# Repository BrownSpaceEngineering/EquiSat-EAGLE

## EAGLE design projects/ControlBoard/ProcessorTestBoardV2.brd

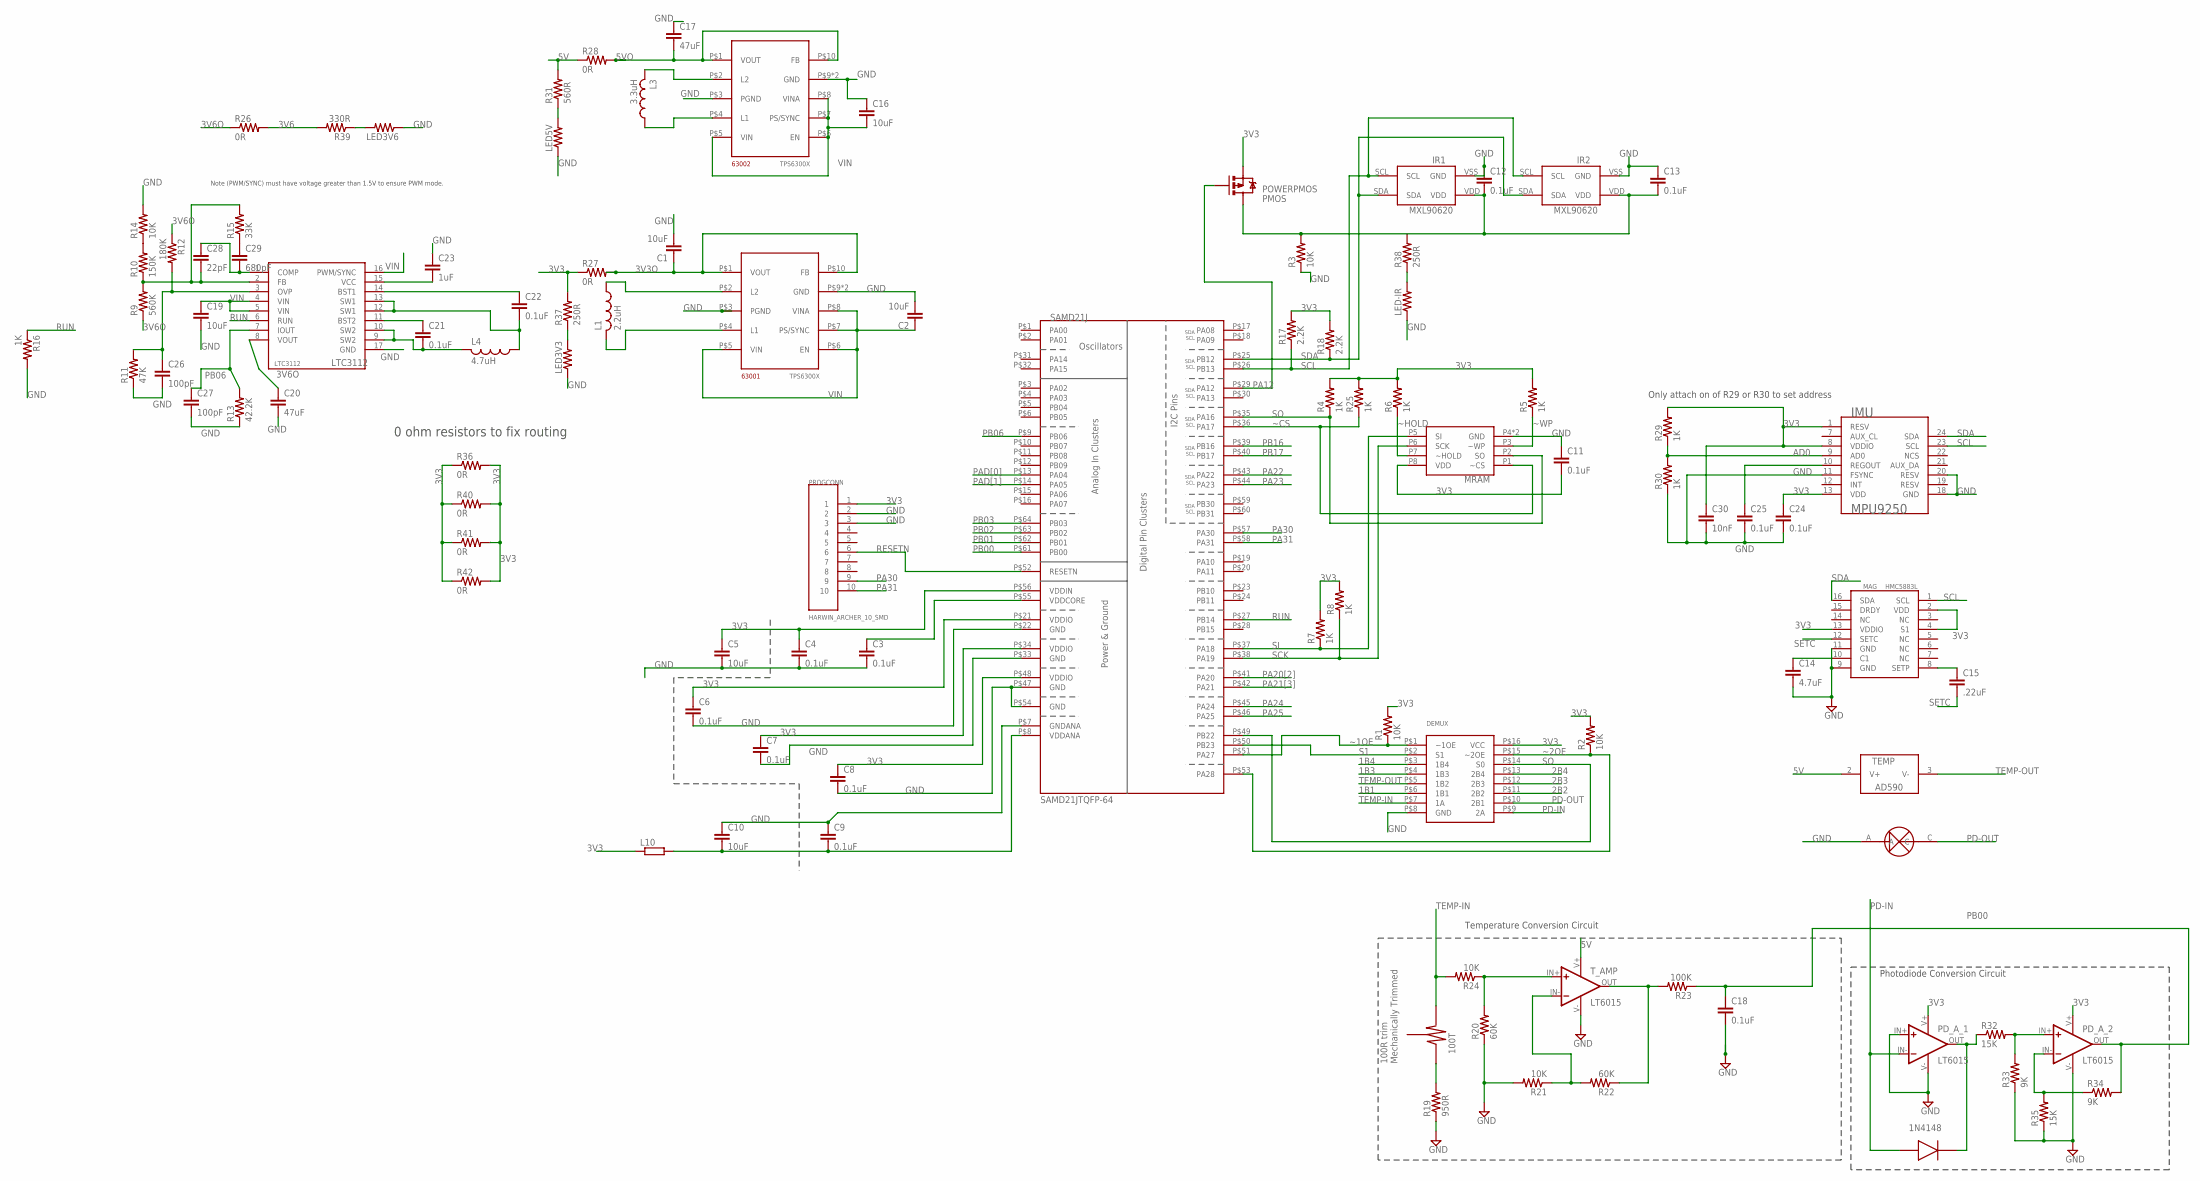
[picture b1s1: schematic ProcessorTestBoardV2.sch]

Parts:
1N4148: 1N4148WS; SOD-323F
100T: TRIMPOT-TC33; TC33X-2
63001, 63002: TPS6300X; QFN10_POWERPAD
C1, C2, C5, C10: 10uF; 0805
C3, C4, C6, C7, C8, C9, C11, C12, C13, C18, C24, C25: 0.1uF; 0805
C14: 4.7uF; 0805; MPN 08056D475KAT2A
C15: .22uF; 0805; MPN 08053C224KAT2A
C16: 10uF; 0603-CAP; MPN C1608X5R1A225K080AC
C17: 47uF; 0603-CAP; MPN EMK107B7474KA-T
C19: 10uF; 0603-CAP
C20: 47uF; 0805; MPN EMK107B7474KA-T
C21, C22: 0.1uF; 0603-CAP; MPN 0603YC104JAT2A
C23: 1uF; 0603-CAP
C26, C27: 100pF; 0805; MPN 08051A101J4T4A
C28: 22pF; 0805; MPN 08051A220JAT2A
C29: 680pF; 0805; MPN 08055C681KAT2A
C30: 10nF; 0805
DEMUX: SN74CBTLV3253; SOIC16R
IMU: MPU9250; QFN-24-3X3
IR1, IR2: MXL90620
L1: 2.2uH; L3225M
L3: 3.3uH; L3225M; MPN JMK212BJ335KG-T
L4: 4.7uH; L3225M
L10: R-EU_R0805; R0805
LED3V3, LED3V6, LED5V: RESISTOR; 0805
LED-IR: RESISTOR; 0805
LTC3112: LTC3112; DHD16; MPN LTC3112EFE#PBF
MAG: HMC5883L; MPN HMC5883L-TR
MRAM: MR25H10CDC; 8PXMO-229
PD: PHOTODETECTOR; PHOTODECTORDEVICE2
PD_A_1, PD_A_2: LT6015; SOT23-5
PMOS: POWERPMOS; SO08
PROGCONN: HARWIN_ARCHER_10_SMD
R1, R2, R3, R14, R21, R24: 10K; 0805
R4, R5, R6, R7, R8, R16, R25, R29, R30: 1K; 0805
R9: 560K; 0805; MPN MC01W08051560K
R10: 150K; 0805
R11: 47K; 0805
R12: 180K; 0805; MPN ERJ-6GEYJ184V
R13: 42.2K; 0805
R15: 33K; 0805
R17, R18: 2.2K; 0805; MPN SR1-0805-222
R19: 950R; 0805
R20, R22: 60K; 0805
R23: 100K; 0805
R26, R27, R28, R36, R40, R41, R42: 0R; 0805
R31: 560R; 0805
R32, R35: 15K; 0805
R33, R34: 9K; 0805
R37, R38: 250R; 0805
R39: 330R; 0805
SAMD21J: SAMD21JTQFP-64; TQFP-64
TEMP: AD590; 8SOIC
T_AMP: LT6015; SOT23-5

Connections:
1B1: DEMUX.P$6 (1B1)
1B3: DEMUX.P$4 (1B3)
1B4: DEMUX.P$3 (1B4)
2B2: DEMUX.P$11 (2B2)
2B3: DEMUX.P$12 (2B3)
2B4: DEMUX.P$13 (2B4)
3V3: C4.1, C5.1, C6.1, C7.1, C8.1, C11.2, C24.1, C30.1, DEMUX.P$16 (VCC), IMU.1 (RESV), IMU.8 (VDDIO), IMU.13 (VDD), L10.1, MAG.2 (VDD), MAG.4 (S1), MAG.13 (VDDIO), MRAM.P8 (VDD), PD_A_1.V+, PD_A_2.V+, PMOS.1 (S), PMOS.2 (S), PMOS.3 (S), PROGCONN.1, R1.2, R2.2, R4.2, R5.2, R6.2, R7.2, R8.2, R17.2, R18.2, R25.2, R27.1, R29.2, R36.1, R36.2, R37.2, R40.1, R40.2, R41.1, R41.2, R42.1, R42.2, SAMD21J.P$21 (VDDIO), SAMD21J.P$34 (VDDIO), SAMD21J.P$48 (VDDIO), SAMD21J.P$56 (VDDIN)
3V3O: 63001.P$1 (VOUT), 63001.P$10 (FB), C1.1, R27.2
3V6: R26.2, R39.2
3V6O: C20.1, LTC3112.8 (VOUT), R9.1, R12.1, R26.1
5V: R28.1, R31.2, TEMP.2 (V+), T_AMP.V+
5VO: 63002.P$1 (VOUT), 63002.P$10 (FB), C17.2, R28.2
AD0: IMU.9 (AD0), R29.1, R30.2
GND: 63001.P$3 (PGND), 63001.P$9 (GND), 63001.PAD (GND), 63002.P$3 (PGND), 63002.P$9 (GND), 63002.PAD (GND), C1.2, C2.2, C3.2, C4.2, C5.2, C6.2, C7.2, C8.2, C9.1, C10.1, C11.1, C12.1, C13.1, C14.2, C16.1, C17.1, C18.2, C19.2, C20.2, C23.1, C24.2, C25.2, C26.2, C27.2, C30.2, DEMUX.P$8 (GND), IMU.11 (FSYNC), IMU.18 (GND), IMU.20 (RESV), IR1.VSS (GND), IR2.VSS (GND), LED3V3.1, LED3V6.1, LED5V.1, LED-IR.1, LTC3112.17 (GND), MAG.9 (GND), MAG.11 (GND), MRAM.P4 (GND), MRAM.P9 (GND), PD.A, PD_A_1.IN+, PD_A_1.V-, PD_A_2.V-, PROGCONN.2, PROGCONN.3, R3.1, R11.1, R13.1, R14.2, R16.2, R19.1, R20.1, R21.2, R30.1, R33.1, R35.1, SAMD21J.P$7 (GNDANA), SAMD21J.P$22 (GND), SAMD21J.P$33 (GND), SAMD21J.P$47 (GND), SAMD21J.P$54 (GND), T_AMP.V-
unnamed: C12.2, C13.2, IR1.VDD, IR2.VDD, PMOS.5 (D), PMOS.6 (D), PMOS.7 (D), PMOS.8 (D), R3.2
unnamed: 63001.P$4 (L1), L1.2
unnamed: 63001.P$2 (L2), L1.1
unnamed: C21.1, LTC3112.11 (BST2)
unnamed: C22.1, LTC3112.14 (BST1)
unnamed: C23.2, LTC3112.15 (VCC)
unnamed: C14.1, MAG.10 (C1)
unnamed: C3.1, SAMD21J.P$55 (VDDCORE)
unnamed: R20.2, R24.1, T_AMP.IN+
unnamed: R22.1, R23.2, T_AMP.OUT
unnamed: R21.1, R22.2, T_AMP.IN-
unnamed: 1N4148.CATHODE, PD_A_1.OUT, R32.1
unnamed: 100T.P$1 (1), R19.2
unnamed: C25.1, IMU.10 (REGOUT)
unnamed: PD_A_2.IN+, R32.2, R33.2
unnamed: LED-IR.2, R38.1
unnamed: C9.2, C10.2, L10.2, SAMD21J.P$8 (VDDANA)
unnamed: PD_A_2.IN-, R34.1, R35.2
unnamed: LED3V6.2, R39.1
unnamed: LED5V.2, R31.1
unnamed: LED3V3.2, R37.1
unnamed: C15.1, MAG.8 (SETP)
unnamed: C22.2, L4.1, LTC3112.12 (SW1), LTC3112.13 (SW1)
unnamed: 63002.P$2 (L2), L3.2
unnamed: 63002.P$4 (L1), L3.1
unnamed: C21.2, L4.2, LTC3112.9 (SW2), LTC3112.10 (SW2)
unnamed: C28.2, LTC3112.2 (FB), R9.2, R10.1, R15.2
unnamed: C26.1, LTC3112.3 (OVP), R11.2, R12.2
unnamed: C29.1, R15.1
unnamed: C28.1, C29.2, LTC3112.1 (COMP)
unnamed: R10.2, R14.1
PA12: PMOS.4 (G), SAMD21J.P$29 (PA12)
PA20[2]: SAMD21J.P$41 (PA20)
PA21[3]: SAMD21J.P$42 (PA21)
PA22: SAMD21J.P$43 (PA22)
PA23: SAMD21J.P$44 (PA23)
PA24: SAMD21J.P$45 (PA24)
PA25: SAMD21J.P$46 (PA25)
PA30: PROGCONN.9, SAMD21J.P$57 (PA30)
PA31: PROGCONN.10, SAMD21J.P$58 (PA31)
PAD[0]: SAMD21J.P$13 (PA04)
PAD[1]: SAMD21J.P$14 (PA05)
PB00: C18.1, PD_A_2.OUT, R23.1, R34.2, SAMD21J.P$61 (PB00)
PB01: SAMD21J.P$62 (PB01)
PB02: SAMD21J.P$63 (PB02)
PB03: SAMD21J.P$64 (PB03)
PB06: C27.1, LTC3112.7 (IOUT), R13.2, SAMD21J.P$9 (PB06)
PB16: SAMD21J.P$39 (PB16)
PB17: SAMD21J.P$40 (PB17)
PD-IN: 1N4148.ANODE, DEMUX.P$9 (2A), PD_A_1.IN-
PD-OUT: DEMUX.P$10 (2B1), PD.C
RESETN: PROGCONN.6, SAMD21J.P$52 (RESETN)
RUN: LTC3112.6 (RUN), R16.1, SAMD21J.P$27 (PB14)
S1: DEMUX.P$2 (S1), SAMD21J.P$50 (PB23)
SCK: MRAM.P6 (SCK), R8.1, SAMD21J.P$38 (PA19)
SCL: IMU.23 (SCL), IR1.SCL, IR2.SCL, MAG.1 (SCL), R17.1, SAMD21J.P$26 (PB13)
SDA: IMU.24 (SDA), IR1.SDA, IR2.SDA, MAG.16 (SDA), R18.1, SAMD21J.P$25 (PB12)
SETC: C15.2, MAG.12 (SETC)
SI: MRAM.P5 (SI), R7.1, SAMD21J.P$37 (PA18)
SO: DEMUX.P$14 (S0), MRAM.P2 (SO), R4.1, SAMD21J.P$35 (PA16), SAMD21J.P$49 (PB22)
TEMP-IN: 100T.P$3 (3), DEMUX.P$7 (1A), R24.2
TEMP-OUT: DEMUX.P$5 (1B2), TEMP.3 (V-)
VIN: 63001.P$5 (VIN), 63001.P$6 (EN), 63001.P$7 (PS/SYNC), 63001.P$8 (VINA), 63002.P$5 (VIN), 63002.P$6 (EN), 63002.P$7 (PS/SYNC), 63002.P$8 (VINA), C2.1, C16.2, C19.1, LTC3112.4 (VIN), LTC3112.5 (VIN), LTC3112.16 (PWM/SYNC)
~1OE: DEMUX.P$1 (~1OE), R1.1, SAMD21J.P$51 (PA27)
~2OE: DEMUX.P$15 (~2OE), R2.1, SAMD21J.P$53 (PA28)
~CS: MRAM.P1 (~CS), R25.1, SAMD21J.P$36 (PA17)
~HOLD: MRAM.P7 (~HOLD), R6.1
~WP: MRAM.P3 (~WP), R5.1

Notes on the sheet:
Note (PWM/SYNC) must have voltage greater than 1.5V to ensure PWM mode.
Temperature Conversion Circuit
100R trim Mechanically Trimmed
Photodiode Conversion Circuit
Only attach on of R29 or R30 to set address
0 ohm resistors to fix routing

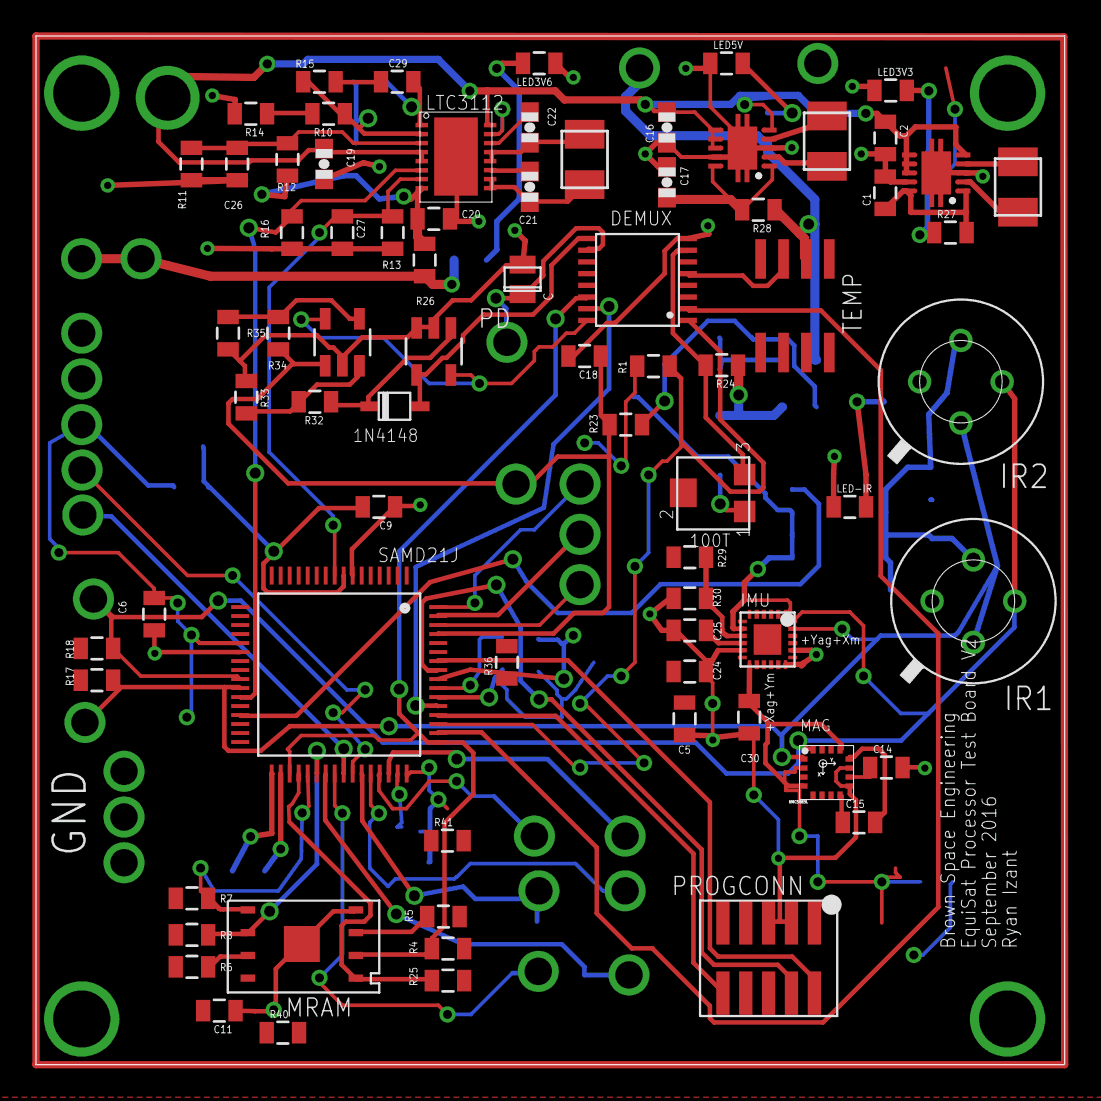
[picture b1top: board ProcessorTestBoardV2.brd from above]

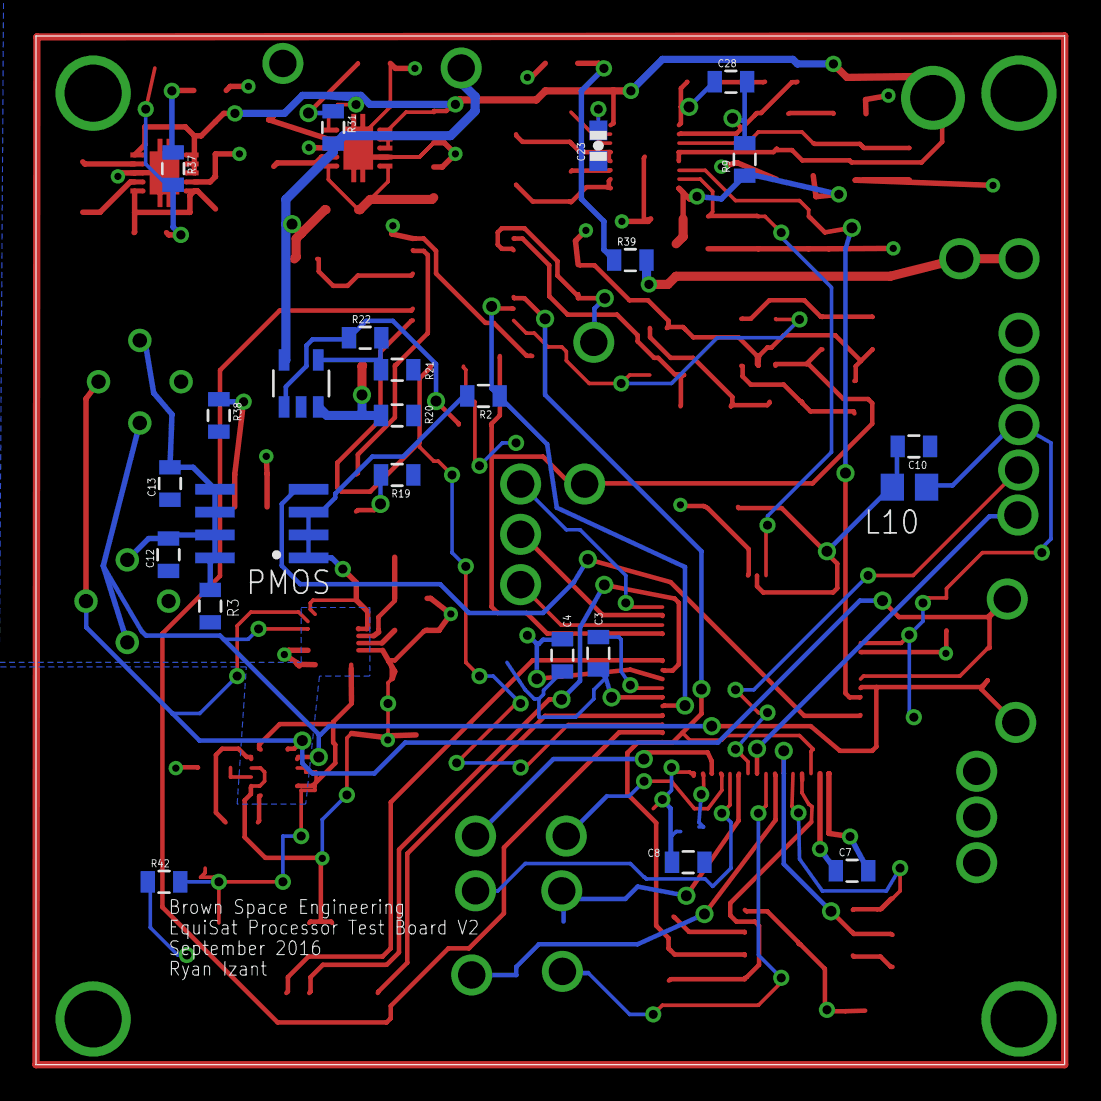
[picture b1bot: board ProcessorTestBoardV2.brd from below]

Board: 2 copper layers, 57.1 x 57.1 mm, 99 parts (24 on the bottom side), 63 nets.

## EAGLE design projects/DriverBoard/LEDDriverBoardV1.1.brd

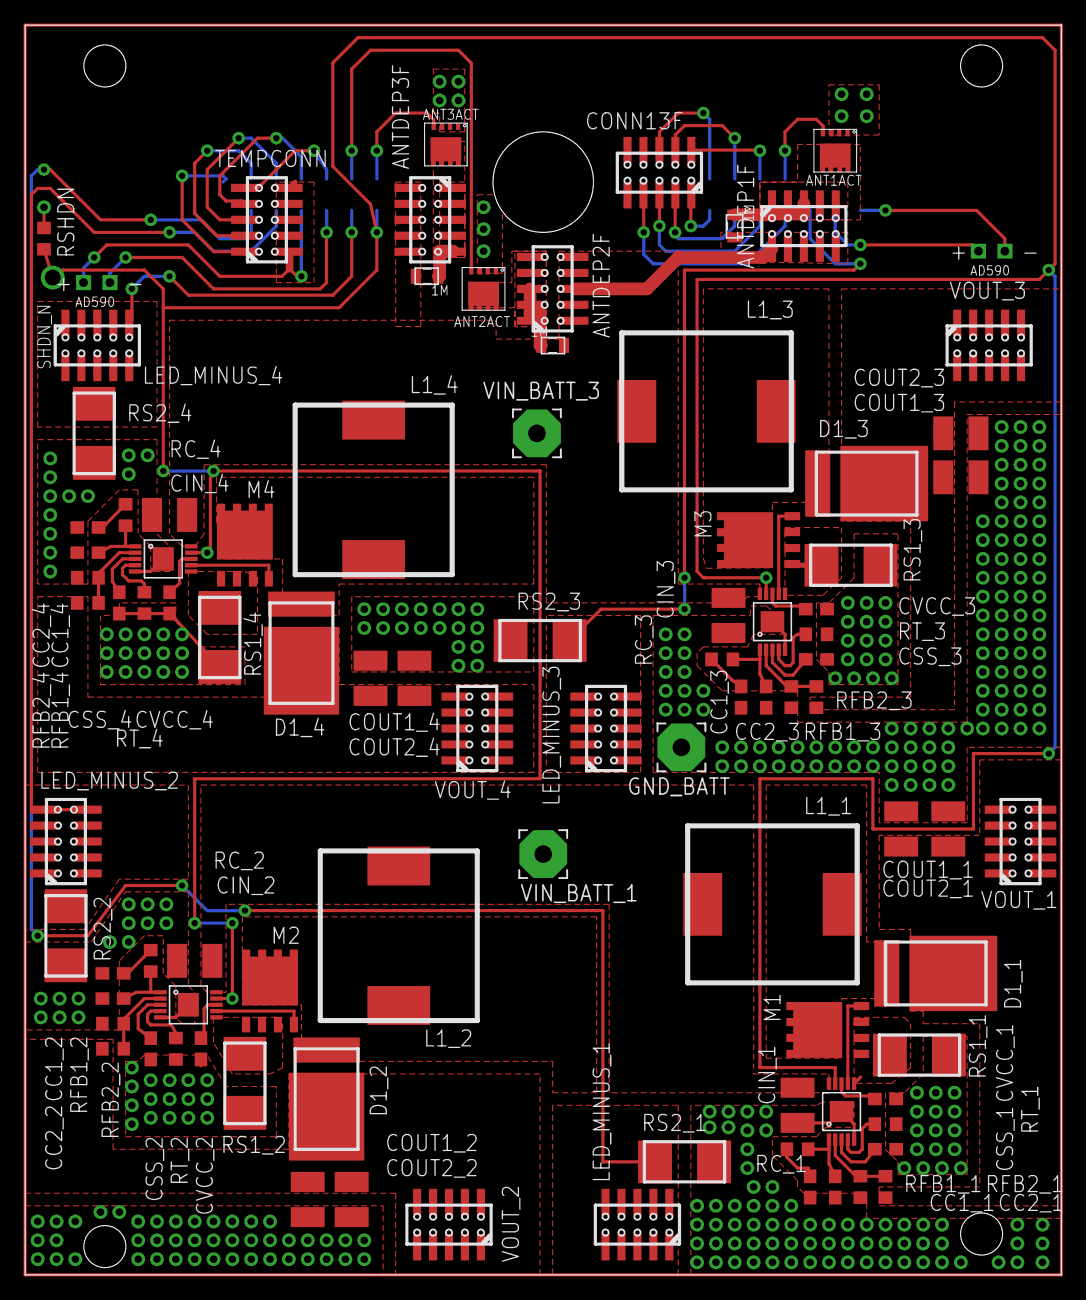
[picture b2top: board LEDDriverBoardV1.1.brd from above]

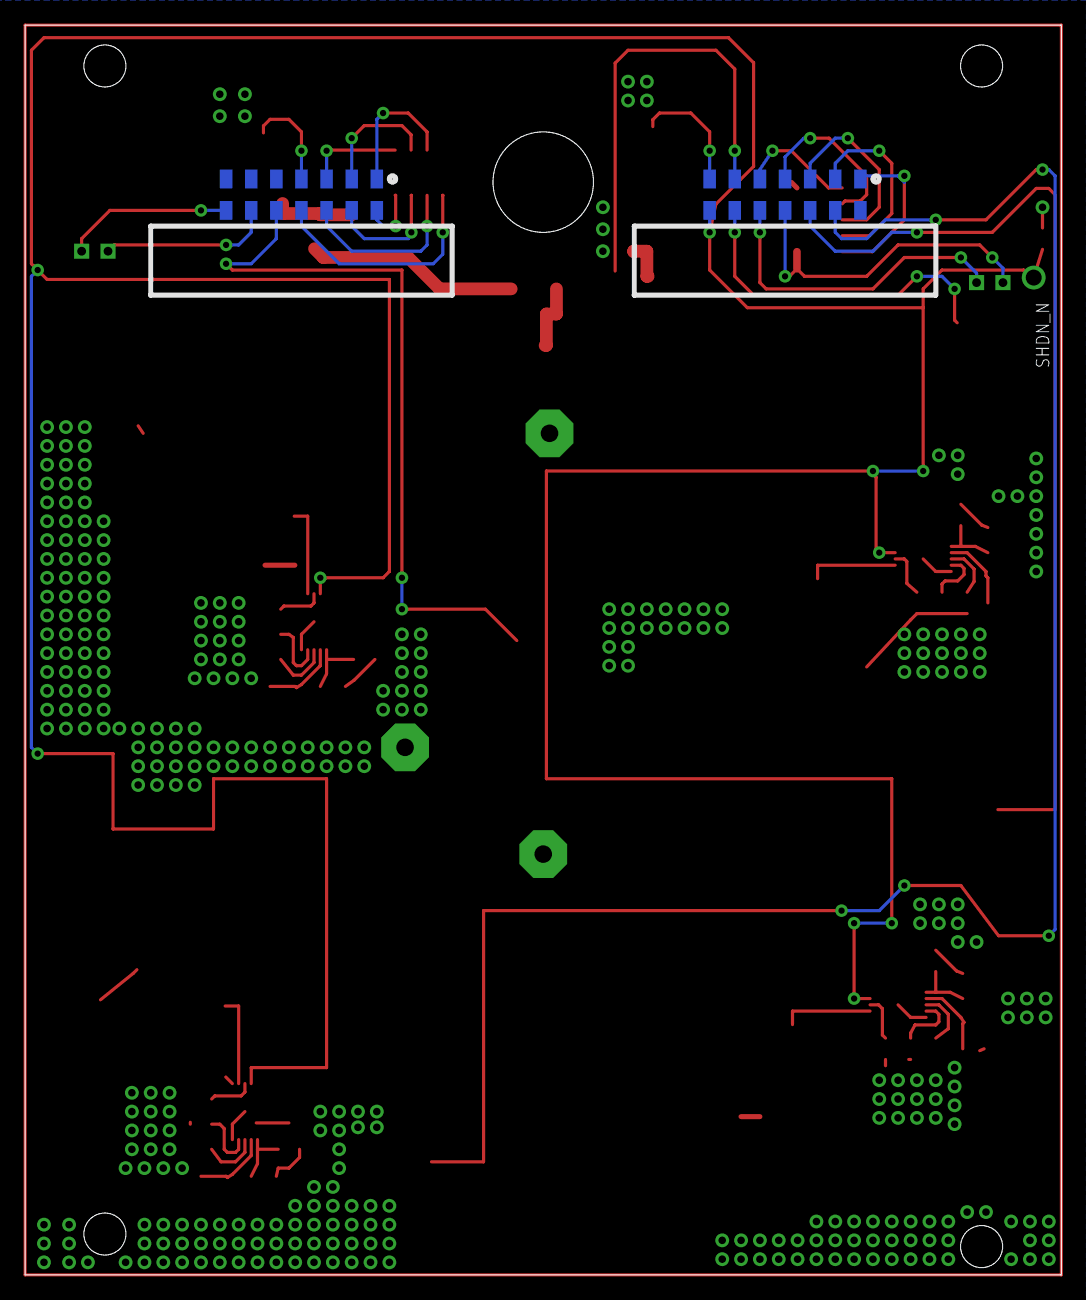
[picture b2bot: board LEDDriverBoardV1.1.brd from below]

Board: 2 copper layers, 82.5 x 99.5 mm, 95 parts (2 on the bottom side), 70 nets.

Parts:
ANT1ACT, ANT2ACT, ANT3ACT: AON7292; DFN3.3X3.3
ANTDEP1F, ANTDEP2F, ANTDEP3F: 10PINFEMALE
CC1_1, CC1_2, CC1_3, CC1_4: 22n; C0603
CC2_1, CC2_2, CC2_3, CC2_4: 100p; C0603
CIN_1, CIN_2, CIN_3, CIN_4: 10u; C1210
CONN13F: 10PINFEMALE
COUT1_1, COUT1_2, COUT1_3, COUT1_4, COUT2_1, COUT2_2, COUT2_3, COUT2_4: 10u; C1210
CSS_1, CSS_2, CSS_3, CSS_4: 0.1u; C0603
CVCC_1, CVCC_2, CVCC_3, CVCC_4: 4.7u; C0603
D1_1, D1_2, D1_3, D1_4: SMC(Z5-T)
DRIVE3TEMP, DRIVE4TEMP: AD590-TH; AD590TH
DRIVECONN1, DRIVECONN2: HARWIN_14_HORIZONTAL_SMD; 14PINMALE_SMD
GND_BATT: 3,81/1,4
L1_1, L1_2, L1_3, L1_4: 1.5u; SRP1245A
LED_MINUS_1, LED_MINUS_2, LED_MINUS_3, LED_MINUS_4: 10PINFEMALE
M1, M2, M3, M4: POWERFLAT
R1, R2, R3: 1M; 0805
RC_1, RC_2, RC_4: 10k; R0603
RC_3: 10K; R0603
RFB1_1, RFB1_2, RFB1_3, RFB1_4: 1k; R0603
RFB2_1, RFB2_2, RFB2_3, RFB2_4: 22.125k; R0603
RS1_1, RS1_2, RS1_3, RS1_4, RS2_1, RS2_2, RS2_3, RS2_4: 3m; ERJMS4S
RSHDN: 1k; R0603
RT_1, RT_2, RT_3, RT_4: 24.3k; R0603
TEMPCONN: 10PINFEMALE
U1, U2, U3, U4: MSOP10
VIN_BATT_1, VIN_BATT_3: 3,81/1,4
VOUT_1, VOUT_2, VOUT_3, VOUT_4: 10PINFEMALE

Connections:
5V_1: DRIVE4TEMP.P$1, DRIVECONN1.11, TEMPCONN.6, TEMPCONN.7, TEMPCONN.8, TEMPCONN.9, TEMPCONN.10
5V_2: DRIVE3TEMP.P$1, DRIVECONN2.9
FBX_1: RFB1_1.2, RFB2_1.1, U1.P$2
FBX_2: RFB1_2.2, RFB2_2.1, U2.P$2
FBX_3: RFB1_3.2, RFB2_3.1, U3.P$2
FBX_4: RFB1_4.2, RFB2_4.1, U4.P$2
FET_SENSE_1: M1.S1, M1.S2, M1.S3, RS1_1.A, U1.P$6
FET_SENSE_2: M2.S1, M2.S2, M2.S3, RS1_2.A, U2.P$6
FET_SENSE_3: M3.S1, M3.S2, M3.S3, RS1_3.A, U3.P$6
FET_SENSE_4: M4.S1, M4.S2, M4.S3, RS1_4.A, U4.P$6
GATE_1: M1.G, U1.P$7
GATE_2: M2.G, U2.P$7
GATE_3: M3.G, U3.P$7
GATE_4: M4.G, U4.P$7
GND: ANT1ACT.S1, ANT1ACT.S2, ANT1ACT.S3, ANT2ACT.S1, ANT2ACT.S2, ANT2ACT.S3, ANT3ACT.S1, ANT3ACT.S2, ANT3ACT.S3, CC1_1.2, CC1_2.2, CC1_3.2, CC1_4.2, CC2_1.2, CC2_2.2, CC2_3.2, CC2_4.2, CIN_1.2, CIN_2.2, CIN_3.2, CIN_4.2, COUT1_1.2, COUT1_2.2, COUT1_3.2, COUT1_4.2, COUT2_1.2, COUT2_2.2, COUT2_3.2, COUT2_4.2, CSS_1.2, CSS_2.2, CSS_3.2, CSS_4.2, CVCC_1.2, CVCC_2.2, CVCC_3.2, CVCC_4.2, DRIVECONN1.14, GND_BATT.1, RFB1_1.1, RFB1_2.1, RFB1_3.1, RFB1_4.1, RS1_1.B, RS1_2.B, RS1_3.B, RS1_4.B, RS2_1.B, RS2_2.B, RS2_3.B, RS2_4.B, RSHDN.1, RT_1.1, RT_2.1, RT_3.1, RT_4.1, U1.P$5, U1.P$11, U2.P$5, U2.P$11, U3.P$5, U3.P$11, U4.P$5, U4.P$11
G_ANT1: ANT1ACT.G, DRIVECONN2.4
G_ANT2: ANT2ACT.G, DRIVECONN1.6
G_ANT3: ANT3ACT.G, DRIVECONN1.7
INTVCC_1: CVCC_1.1, U1.P$8
INTVCC_2: CVCC_2.1, U2.P$8
INTVCC_3: CVCC_3.1, U3.P$8
INTVCC_4: CVCC_4.1, U4.P$8
LDM_1: D1_1.ANODE, L1_1.P$2, M1.D, M1.D5, M1.D6, M1.D7, M1.D8
LDM_2: D1_2.ANODE, L1_2.P$2, M2.D, M2.D5, M2.D6, M2.D7, M2.D8
LDM_3: D1_3.ANODE, L1_3.P$2, M3.D, M3.D5, M3.D6, M3.D7, M3.D8
LDM_4: D1_4.ANODE, L1_4.P$2, M4.D, M4.D5, M4.D6, M4.D7, M4.D8
LED_SENSE_1: DRIVECONN1.13, LED_MINUS_1.1, LED_MINUS_1.2, LED_MINUS_1.3, LED_MINUS_1.4, LED_MINUS_1.5, LED_MINUS_1.6, LED_MINUS_1.7, LED_MINUS_1.8, LED_MINUS_1.9, LED_MINUS_1.10, RS2_1.A
LED_SENSE_2: DRIVECONN1.12, LED_MINUS_2.1, LED_MINUS_2.2, LED_MINUS_2.3, LED_MINUS_2.4, LED_MINUS_2.5, LED_MINUS_2.6, LED_MINUS_2.7, LED_MINUS_2.8, LED_MINUS_2.9, LED_MINUS_2.10, RS2_2.A
LED_SENSE_3: DRIVECONN2.10, LED_MINUS_3.1, LED_MINUS_3.2, LED_MINUS_3.3, LED_MINUS_3.4, LED_MINUS_3.5, LED_MINUS_3.6, LED_MINUS_3.7, LED_MINUS_3.8, LED_MINUS_3.9, LED_MINUS_3.10, RS2_3.A
LED_SENSE_4: DRIVECONN1.9, LED_MINUS_4.1, LED_MINUS_4.2, LED_MINUS_4.3, LED_MINUS_4.4, LED_MINUS_4.5, LED_MINUS_4.6, LED_MINUS_4.7, LED_MINUS_4.8, LED_MINUS_4.9, LED_MINUS_4.10, RS2_4.A
unnamed: CC1_2.1, RC_2.1
unnamed: CC1_3.1, RC_3.1
unnamed: CC1_1.1, RC_1.1
unnamed: CC1_4.1, RC_4.1
unnamed: DRIVECONN1.1, TEMPCONN.1
unnamed: DRIVECONN1.2, TEMPCONN.2
unnamed: DRIVECONN1.3, TEMPCONN.3
unnamed: DRIVECONN1.4, TEMPCONN.4
unnamed: DRIVECONN1.5, TEMPCONN.5
unnamed: CONN13F.1, DRIVECONN2.14
unnamed: CONN13F.2, DRIVECONN2.13
unnamed: CONN13F.3, DRIVECONN2.12
unnamed: CONN13F.4, DRIVECONN2.11
unnamed: CONN13F.8, DRIVECONN2.1
unnamed: CONN13F.9, DRIVECONN2.2
unnamed: DRIVE4TEMP.P$2, DRIVECONN1.10
unnamed: CONN13F.10, DRIVECONN2.3
unnamed: ANT3ACT.D1, ANT3ACT.D2, ANT3ACT.D3, ANT3ACT.D4, ANT3ACT.D5, ANTDEP3F.1, ANTDEP3F.2, ANTDEP3F.3, ANTDEP3F.4, ANTDEP3F.5, R2.1
unnamed: ANT2ACT.D1, ANT2ACT.D2, ANT2ACT.D3, ANT2ACT.D4, ANT2ACT.D5, ANTDEP2F.1, ANTDEP2F.2, ANTDEP2F.3, ANTDEP2F.4, ANTDEP2F.5, R1.1
unnamed: ANT1ACT.D1, ANT1ACT.D2, ANT1ACT.D3, ANT1ACT.D4, ANT1ACT.D5, ANTDEP1F.1, ANTDEP1F.2, ANTDEP1F.3, ANTDEP1F.4, ANTDEP1F.5, R3.1
unnamed: DRIVE3TEMP.P$2, DRIVECONN2.8
RT_1: RT_1.2, U1.P$4
RT_2: RT_2.2, U2.P$4
RT_3: RT_3.2, U3.P$4
RT_4: RT_4.2, U4.P$4
SHDN_N: DRIVECONN1.8, RSHDN.2, U1.P$9, U2.P$9, U3.P$9, U4.P$9
SS_1: CSS_1.1, U1.P$3
SS_2: CSS_2.1, U2.P$3
SS_3: CSS_3.1, U3.P$3
SS_4: CSS_4.1, U4.P$3
VC_1: CC2_1.1, RC_1.2, U1.P$1
VC_2: CC2_2.1, RC_2.2, U2.P$1
VC_3: CC2_3.1, RC_3.2, U3.P$1
VC_4: CC2_4.1, RC_4.2, U4.P$1
VIN_BATT_1: CIN_1.1, CIN_2.1, L1_1.P$1, L1_2.P$1, U1.P$10, U2.P$10, VIN_BATT_1.1
VIN_BATT_3: ANTDEP1F.6, ANTDEP1F.7, ANTDEP1F.8, ANTDEP1F.9, ANTDEP1F.10, ANTDEP2F.6, ANTDEP2F.7, ANTDEP2F.8, ANTDEP2F.9, ANTDEP2F.10, ANTDEP3F.6, ANTDEP3F.7, ANTDEP3F.8, ANTDEP3F.9, ANTDEP3F.10, CIN_3.1, CIN_4.1, L1_3.P$1, L1_4.P$1, R1.2, R2.2, R3.2, U3.P$10, U4.P$10, VIN_BATT_3.1
VOUT_1: COUT1_1.1, COUT2_1.1, D1_1.CATHODE, RFB2_1.2, VOUT_1.1, VOUT_1.2, VOUT_1.3, VOUT_1.4, VOUT_1.5, VOUT_1.6, VOUT_1.7, VOUT_1.8, VOUT_1.9, VOUT_1.10
VOUT_2: COUT1_2.1, COUT2_2.1, D1_2.CATHODE, RFB2_2.2, VOUT_2.1, VOUT_2.2, VOUT_2.3, VOUT_2.4, VOUT_2.5, VOUT_2.6, VOUT_2.7, VOUT_2.8, VOUT_2.9, VOUT_2.10
VOUT_3: COUT1_3.1, COUT2_3.1, D1_3.CATHODE, RFB2_3.2, VOUT_3.1, VOUT_3.2, VOUT_3.3, VOUT_3.4, VOUT_3.5, VOUT_3.6, VOUT_3.7, VOUT_3.8, VOUT_3.9, VOUT_3.10
VOUT_4: COUT1_4.1, COUT2_4.1, D1_4.CATHODE, RFB2_4.2, VOUT_4.1, VOUT_4.2, VOUT_4.3, VOUT_4.4, VOUT_4.5, VOUT_4.6, VOUT_4.7, VOUT_4.8, VOUT_4.9, VOUT_4.10

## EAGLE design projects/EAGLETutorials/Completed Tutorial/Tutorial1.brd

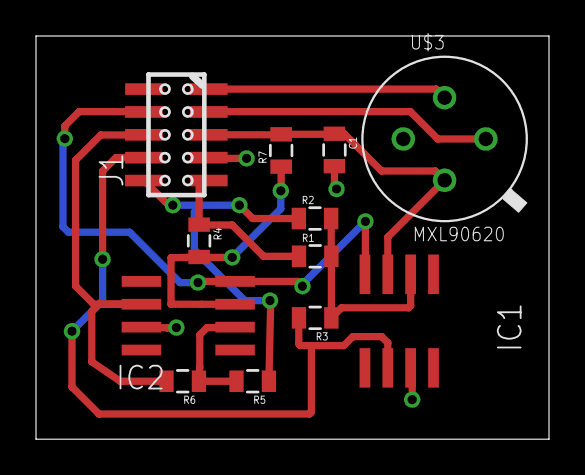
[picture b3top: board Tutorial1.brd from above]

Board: 2 copper layers, 28.5 x 22.4 mm, 12 parts (0 on the bottom side), 12 nets.

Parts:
C1: 0805
IC1, IC2: AD820R; SO8
J1: 10PINFEMALE
R1, R2, R4, R5: 1K; 0805
R3, R6, R7: 5K; 0805
U$3: MXL90620

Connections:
3V3: C1.2, IC1.7, IC2.7, J1.4, U$3.VDD
-3V3: IC1.4, IC2.4, J1.9
DIFFOUT: IC2.6, J1.8, R6.2
GND: C1.1, IC1.3, J1.3, R7.2, U$3.VSS
IN_1: J1.5, R1.1, R4.1
IN_2: J1.6, R2.1, R5.1
unnamed: IC1.2, R1.2, R2.2, R3.1
unnamed: J1.1, U$3.SDA
unnamed: J1.2, U$3.SCL
unnamed: IC2.2, R5.2, R6.1
unnamed: IC2.3, R4.2, R7.1
SUMOUT: IC1.6, J1.7, R3.2
